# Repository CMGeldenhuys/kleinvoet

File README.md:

# Kleinvoet

*Kleinvoet* is a self-contained low-cost passive acoustic monitoring device.
The recorder was initially designed for distributed infrasonic (8Hz)
localisation, and features accurate temporal synchronisation through the use of
an onboard GNSS module.

The recorder is capable of 24-bit stereo recording at a variable sampling rate
of 8kHz to 192kHz.  The recordings along with timestamp and operational log
information is stored on a microSD card.  The recordings are stored as a series of
256MiB WAV files.

Firmware is available at [CMGeldenhuys/kleinvoet-firmware](https://github.com/CMGeldenhuys/kleinvoet-firmware).
All relevant production files such as panelised gerbers, bill of materials and work orders can be found in the `production` folder in the repo.
Additionally, the PCB layout and schematics for the Kleinvoet recorders can be found in the `docs/pcb_single`, `docs/pcb_panel` and `docs/schematics` directories, respectively.

## Example Recordings

- [Artificial elephant call](docs/rec/elephant_call_1000hz_lpf_normalised.wav) (recorded 150m from source, 1000Hz low pass filtered and normalised)

## SD Card Recommendations

In order to keep cost down, Kleinvoet does not make use of external SRAM. As such
the I/O buffer is limited to the internal SRAM of the MCU. It is thus
recommended using a class-10 high quality microSD card. Before a long-running
experiment it is also recommended to do a "low-level" format of the microSD
card. This will improve the write performance which is required at higher
sampling rates.

## Assembly

To assemble a Kleinvoet node, one will require all the electronic
components listed in the bill of materials (BOM), as well as have the necessary
PCBs manufactured. The provided gerber files can be sent directly to most PCB
fabrication houses. To assemble the boards, one can use either hot-air or plate
reflow soldering methods. The [interactive BOM](bom/ibom.html) might be useful
when placing the components manually.

| PCB | Back | Front |
| --- | --- | --- |
|Main Board|  |  |
|GNSS Board|  |  |
|Microphone Board|  |  |

Once all the components have been soldered to their respective boards, the
firmware can be flashed to the MCU using an [ST
Link](https://www.st.com/en/development-tools/st-link-v2.html)
debugger/programmer. However, not tested, any JTAG debugger/programmer should
work. There are also open-source projects that use another STM32 MCU as a
debugger/programmer ([blackmagic
probe](https://github.com/blackmagic-debug/blackmagic)).

Once programmed, proceed by connecting the GNSS header (marked on the respective
PCBs) of the main board to the GNSS daughter board. Note, this connector can be
reversed and the user should double-check that the **SYNC** pin (marked with an
triangle) on the main board is connected to the **SYNC** pin of the GNSS board.
If your use case does not require timestamping, the GNSS board can be omitted.
Next, connect the microphone boards to their respective channels, marked on the
main board's PCB as **CH1** and **CH2**. These connectors are keyed, and thus
It can only be connected one way.

If the user chooses to omit the weatherproof housing, Kleinvoet can be held
together with two rubber bands. The notches on the main and GNSS boards snap
together with the holes in the microphone boards to form a cube.

In order to assemble the weatherproof housing, start by placing the LiPo battery
in the lid of the enclosure. Thread the battery lead through the hole of the
main PCB adaptor plate. Next, mount the plate to the lid, keeping the battery in
place. One can then proceed to mount the main PCB to the adaptor. Next mount
the GNSS adaptor plate in the bottom of the Bocube housing, and mount the GNSS
PCB to the adaptor. If using the windshielding, remove the backing paper and
paste it firmly over the microphone inlets, (Note, the MEMS microphones used are
bottom port microphone and thus the inlet port is on the bottom side of the PCB.
The area to place the shielding foam is marked by a hashed circle) Install the
microphone board spacers, ensuring that the mounting holes align properly. The
microphone board assembly can now be mounted to the inside of the Bocube
housing. Next, connect the individual daughter boards (GNSS and microphone PCBs)
to their respective connectors on the main board.

Insert a FAT32 formatted microSD card into the main board and plug in the
battery. The node will perform a self test, followed by a self configuration
stage and then begin recordings. This process might take up to 10 seconds. Once
the node is configured, a solid amber light will be illuminated. Please refer to
the troubleshooting section if this is not the case.

## Operation

### Startup Procedure

1. Ensure the device is powered off.
1. Insert a FAT32 formatted microSD into the main board.
1. Connect the battery to the main board.
1. Wait for the solid amber indicator LED.
1. (Optional) Close weatherproof housing.

### Shutdown Procedure

1. Press the **USER** button (marked on the PCB of the main board).
1. The status indicators should start flashing repeatedly.
1. Disconnect the battery.
1. Remove microSD card.

### Status Indicators
Each PCB contains a *RED* status LED, used to indicate that the board has power.
On the main PCB there are two running status indication LEDs (*AMBER* and *BLUE*).

When **running**, the *AMBER* LED will remain solid. Once a GNSS lock (both time
and location) is obtained, the *BLUE* LED will pulse briefly every 10 seconds
(default).

If an unrecoverable error has occurred, the two status LEDs (*AMBER* and *BLUE*),
will pulse is quick succession. In this case, the watchdog timer will trigger and
attempt to write the operational log and reset the device. During a catastrophic
failure it might not be possible to write to the microSD card depending on the
error that has occurred.

| State | Blue LED | Amber LED |
| --- | --- | --- |
| Start-up | Blink (1s) | Off |
| Recording | Solid | X |
| GNSS Lock | X | Blink (10s) |
| Catastrophic Error | Strobe | Strobe |

In the table above, '*X*' denotes a "do not care" or irrelevant status. In other
words, it is not an indication of the current device state.

### File Layout

After recording, the following file structure will be present on the microSD card of the respective node.

```
(root)
├── REC_1
│   ├── KV.LOG
│   ├── REC.WAV
│   ├── REC.W01
│   ├── REC.W02
│   ├── REC.W03
│   └── TS.CSV
├── REC_X
│   ├── KV.LOG
│   ├── REC.WXX
│   └── TS.CSV
└── CONF.INI (experimental)
```

Each recording will be stored as a WAVE file in the corresponding `REC_X`
folder. Where the recorder increments `X` for every subsequent recording made on
the device (e.g. `REC_1`, `REC_2` etc.). Inside each recording folder are the
files associated with that recording. Due to the limitation of the FAT32
filesystem each individual recording has to be split up across multiple WAVE
files (e.g.`REC.WAV`, `REC.W01`, etc.). By default, this is in 256 MiB chunks, but
is user configurable Contained in the header of each WAVE file is timestamping
and location information required to synchronise the nodes during offline
processing of the files. A granular log of the timestamping metadata is stored
in `TS.CSV`. A complete operational log is stored in `KV.LOG`, which might deem
useful in troubleshooting a faulty recording node. (Experimental) Currently the
node's configuration is compiled into the device firmware, however, there is a
experimental firmware branch that allows for the configuration to be stored on
the microSD. 

| File/Folder | Purpose |
| --- | --- |
| REC_X | Folder containing all files associated with the particular recording|
| KV.LOG | Operational log of recordings |
| TS.CSV | Timestamping metadata |
| REC.WXX | Audio recording stored as a WAVE file |
| CONF.INI | (Experimental) Runtime configuration file |

## Power Spectral Density Estimates

Provided below are a power spectral density estimates (PSD) generated using
Welch's method. The [Sennheiser MKH 8020](https://sennheiser.com/mkh-8020) was used as a reference microphone and
tested in an acoustically dampened recording studio. These results provide an
estimate of the recording device's frequency response and should not be used
as ground truth measurements where spectral magnitude accuracy is required.
For those types of experiments, we recommenced the use of calibrated reference
sound amplitude measurement equipment.

## Troubleshooting

First ensure the following:
- Power from USB-C not battery, all boards have a solid *RED* LED illuminated
- MicroSD Card is formatted as **FAT32** and inserted
- The respective daughter boards are correctly connected

Enable `LOG_DEST_TTY` in `config.h`. The operational log will be printed in
real-time to the serial console available on the debug/programming port. When
using an *ST Link* debugger, this serial port can be opened using
[Putty](https://www.putty.org/) on Windows, or with the following command on
Linux:
``` sh
screen -b 115200 /dev/ttyACM0
```
The serial port is configured to **115200** baud rate and the standard **8N1**
configuration. Please see the [firmware guide](firmware/README.md) for more
information on setting up the programming environment on a Linux-based system.

## Future Hardware Revisions

- [ ] Dedicated GNSS connector, instead of headers
- [ ] E-Ink Display
- [ ] DFU mode (program without probe)
- [ ] Improved low-power mode (deep sleep)
- [ ] Add BME280 Sensor (temperature, humidity, atmospheric pressure)
- [ ] Battery charging status detection
- [ ] Dedicated power switch
- [ ] External RAM (larger buffer, allows use with low-end SD cards)
- [ ] Allow non-LiPo batteries (eg. alkaline)

## Contributing

We welcome contributions to the project. Unfortunately, hardware cannot be
provided to contributors. However, the [STM32
Nucleo-F446RE](https://www.st.com/en/evaluation-tools/nucleo-f446re.html) can be
used as an firmware development alternative, and is readily available.

## Authors and Acknowledgements

- [Christiaan M. Geldenhuys](https://github.com/CMGeldenhuys)
- [Thomas R. Niesler](https://dsp.sun.ac.za/~trn)

This project formed part of research done by the [Electrical and Electronic
Engineering Department](https://www.ee.sun.ac.za/) at Stellenbosch University.

## License

The Kleinvoet project is licensed under the CERN Open Hardware License version 2
(strongly-reciprocal variant). The license agreement and copyright only partain
to the Kleinvoet recorder design. Third party CAD models and EDA footprints
remain under the original license agreement and copyright of the respective
intellectual property owners.

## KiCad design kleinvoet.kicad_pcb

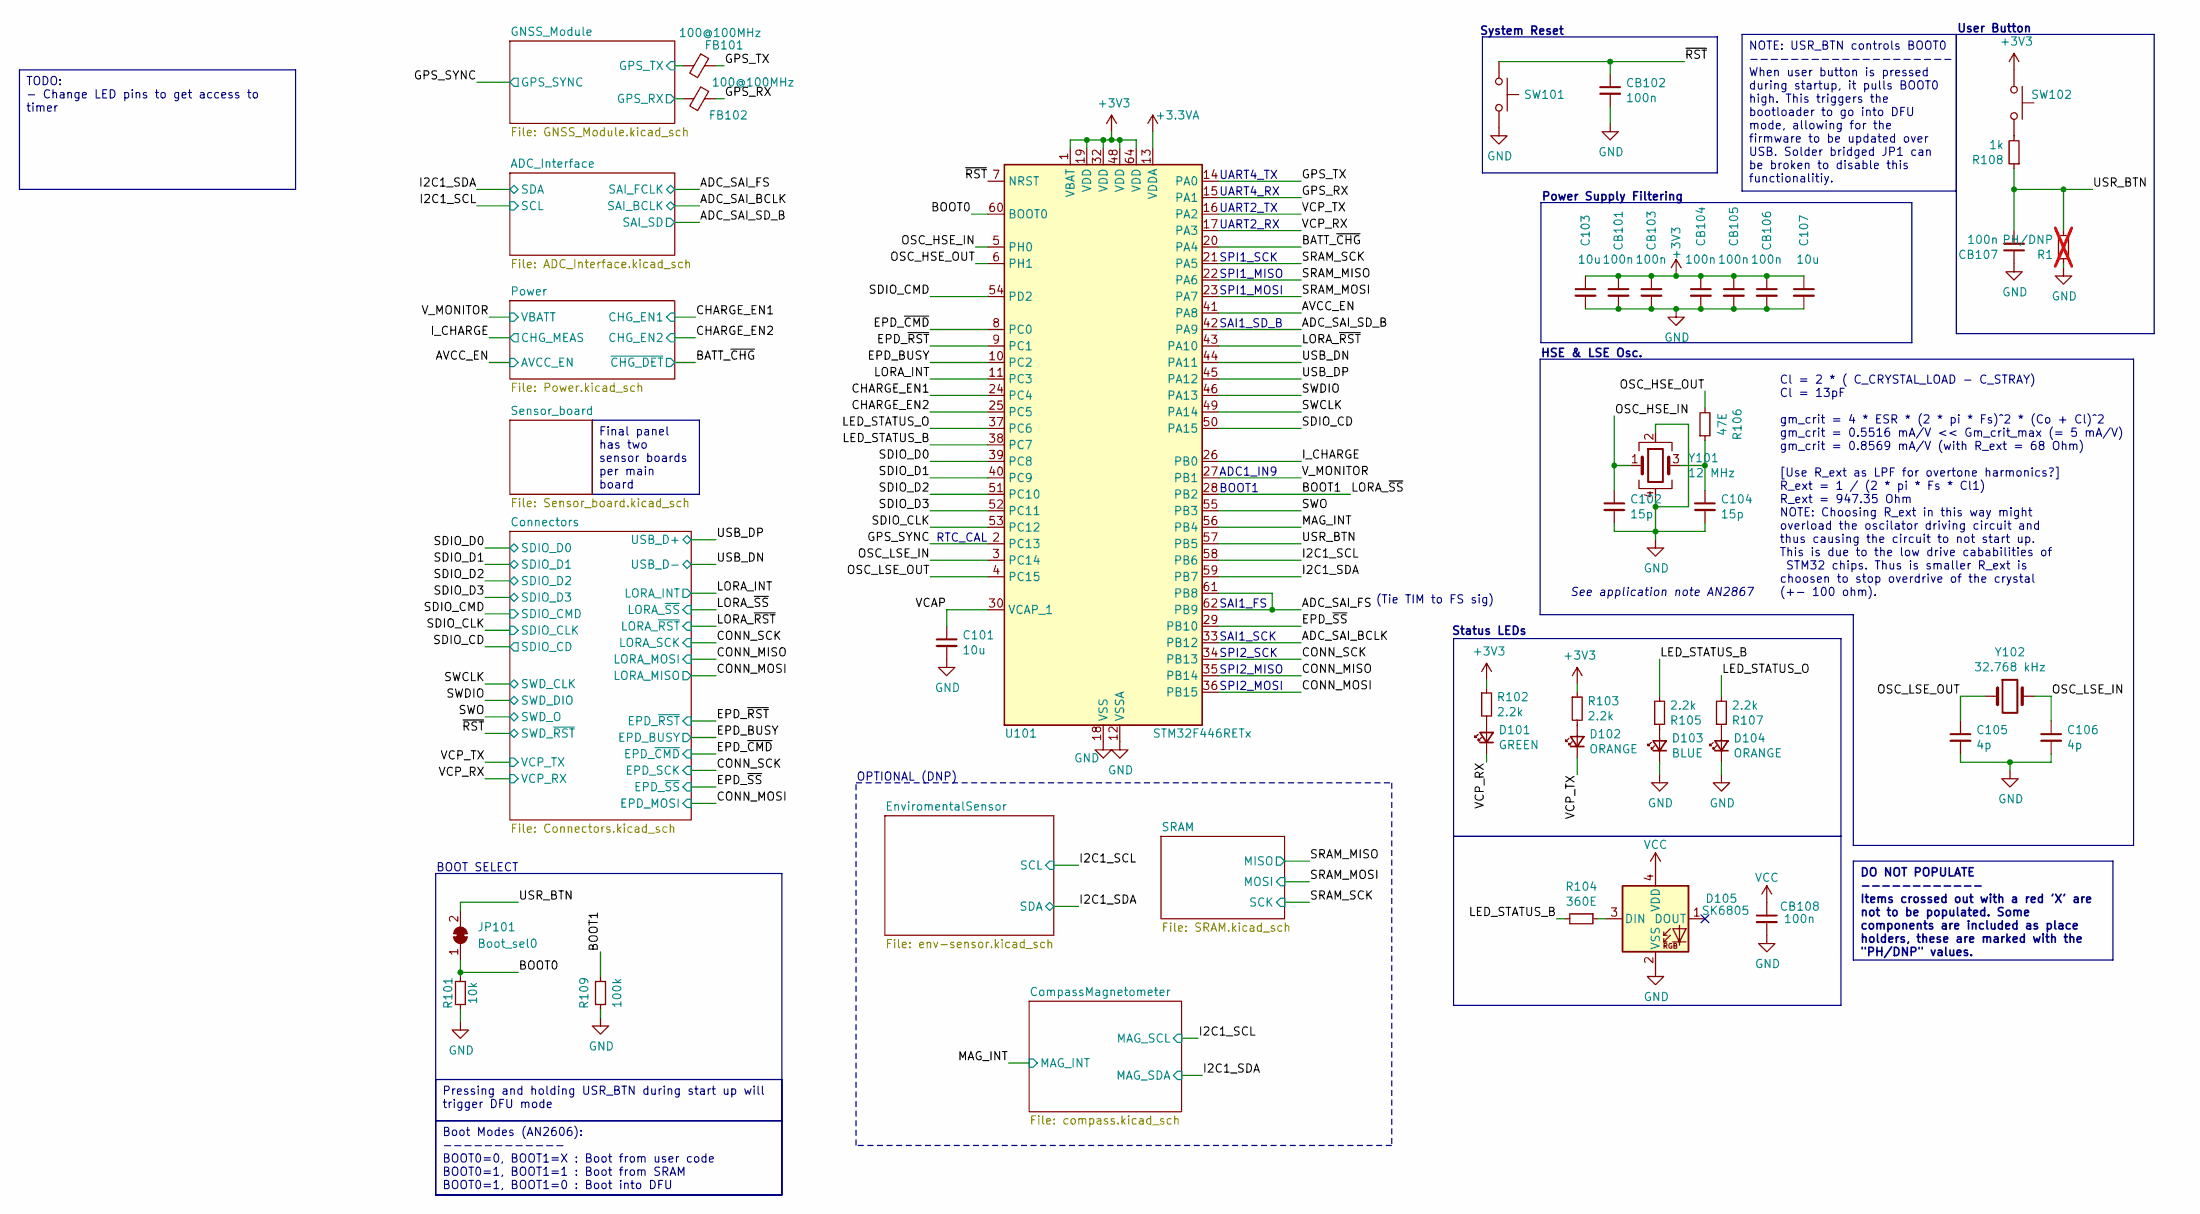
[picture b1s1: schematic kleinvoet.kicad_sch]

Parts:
C101, C103, C107: 10u; C_0402_1005Metric; MPN GRM155R60J106ME05D
C102, C104: 15p; C_0402_1005Metric; MPN GRM1555C1H150GA01D
C105, C106: 4p; C_0402_1005Metric; MPN GJM1555C1H4R0BB01D
CB101, CB102, CB103, CB104, CB105, CB106, CB107, CB108: 100n; C_0402_1005Metric; MPN C0402C104K8PACTU
D101: GREEN; LED_0603_1608Metric_Pad1.05x0.95mm_HandSolder; MPN SMLD12EN1WT86
D102: ORANGE; LED_0603_1608Metric_Pad1.05x0.95mm_HandSolder; MPN SML-D12D8WT86C
D103: BLUE; LED_0603_1608Metric; MPN SMLD12BN1WT86
D104: ORANGE; LED_0603_1608Metric; MPN SML-D12D8WT86C
D105: SK6805; LED_SK6805_PLCC4_2.4x2.7mm_P1.3mm; MPN SK6805-2427 (ALT: 485-4492, 1528-2291-N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
FB101, FB102: 100@100MHz; L_0402_1005Metric; MPN BLM15HD102SN1D
JP101: Boot_sel0; SolderJumper-2_P1.3mm_Bridged_RoundedPad1.0x1.5mm
R1: PH/DNP; R_0402_1005Metric; not fitted
R101: 10k; R_0402_1005Metric; MPN RT0402FRE1310KL
R102, R103, R105, R107: 2.2k; R_0402_1005Metric; MPN RT0402FRE072K2L
R104: 360E; R_0402_1005Metric; MPN RT0402FRE07360RL
R106: 47E; R_0402_1005Metric; MPN RT0402FRE0747RL
R108: 1k; R_0402_1005Metric; MPN RT0402FRE071KL
R109: 100k; R_0402_1005Metric; MPN RT0402FRE07100KL
SW101: RESET; SW_Tactile_SPST_NO_Straight_CK_PTS636Sx25SMTRLFS; MPN PTS636 SM25 SMTR LFS
SW102: USER; SW_Tactile_SPST_NO_Straight_CK_PTS636Sx25SMTRLFS; MPN PTS636 SM25 SMTR LFS
U101: STM32F446RETx; LQFP-64_10x10mm_P0.5mm; MPN STM32F446RCT6
Y101: 12 MHz; ECS-33B; MPN ECS-120-12-33-AEN-TR
Y102: 32.768 kHz; ECX-31B; MPN ECS-.327-7-34B-TR

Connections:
+3.3VA: U101.13 (VDDA); also elsewhere on the board
/ADC_SAI_BCLK: U101.33 (PB12); also elsewhere on the board
/ADC_SAI_FS: U101.61 (PB8), U101.62 (PB9); also elsewhere on the board
/ADC_SAI_SD_B: U101.42 (PA9); also elsewhere on the board
/AVCC_EN: U101.41 (PA8); also elsewhere on the board
/BATT_~CHG: U101.20 (PA4); also elsewhere on the board
/BOOT0: JP101.1 (A), R101.1, U101.60 (BOOT0)
/BOOT1: R109.2, U101.28 (PB2); also elsewhere on the board
/CHARGE_EN1: U101.24 (PC4); also elsewhere on the board
/CHARGE_EN2: U101.25 (PC5); also elsewhere on the board
/CONN_MISO: U101.35 (PB14); also elsewhere on the board
/CONN_MOSI: U101.36 (PB15); also elsewhere on the board
/CONN_SCK: U101.34 (PB13); also elsewhere on the board
/EPD_BUSY: U101.10 (PC2); also elsewhere on the board
/EPD_~CMD: U101.8 (PC0); also elsewhere on the board
/EPD_~RST: U101.9 (PC1); also elsewhere on the board
/EPD_~SS: U101.29 (PB10); also elsewhere on the board
/GNSS_Module/GPS_RX: FB102.1; also elsewhere on the board
/GNSS_Module/GPS_TX: FB101.1; also elsewhere on the board
/GPS_RX: FB102.2, U101.15 (PA1)
/GPS_SYNC: U101.2 (PC13); also elsewhere on the board
/GPS_TX: FB101.2, U101.14 (PA0)
/I_CHARGE: U101.26 (PB0); also elsewhere on the board
/LED_STATUS_B: R104.2, R105.2, U101.38 (PC7)
/LED_STATUS_O: R107.2, U101.37 (PC6)
/LORA_INT: U101.11 (PC3); also elsewhere on the board
/LORA_~RST: U101.43 (PA10); also elsewhere on the board
/MAG_INT: U101.56 (PB4); also elsewhere on the board
/OSC_HSE_IN: C102.1, U101.5 (PH0), Y101.1
/OSC_HSE_OUT: R106.2, U101.6 (PH1)
/OSC_LSE_IN: C106.1, U101.3 (PC14), Y102.2
/OSC_LSE_OUT: C105.1, U101.4 (PC15), Y102.1
/SDIO_CD: U101.50 (PA15); also elsewhere on the board
/SDIO_CLK: U101.53 (PC12); also elsewhere on the board
/SDIO_CMD: U101.54 (PD2); also elsewhere on the board
/SDIO_D0: U101.39 (PC8); also elsewhere on the board
/SDIO_D1: U101.40 (PC9); also elsewhere on the board
/SDIO_D2: U101.51 (PC10); also elsewhere on the board
/SDIO_D3: U101.52 (PC11); also elsewhere on the board
/SRAM_MISO: U101.22 (PA6); also elsewhere on the board
/SRAM_MOSI: U101.23 (PA7); also elsewhere on the board
/SRAM_SCK: U101.21 (PA5); also elsewhere on the board
/SWCLK: U101.49 (PA14); also elsewhere on the board
/SWDIO: U101.46 (PA13); also elsewhere on the board
/SWO: U101.55 (PB3); also elsewhere on the board
/USB_DN: U101.44 (PA11); also elsewhere on the board
/USB_DP: U101.45 (PA12); also elsewhere on the board
/USR_BTN: CB107.2, JP101.2 (B), R1.2, R108.1, U101.57 (PB5)
/VCAP: C101.1, U101.30 (VCAP_1)
/VCP_RX: D101.1 (K), U101.17 (PA3); also elsewhere on the board
/VCP_TX: D102.1 (K), U101.16 (PA2); also elsewhere on the board
/V_MONITOR: U101.27 (PB1); also elsewhere on the board
/~RST: CB102.1, SW101.1, U101.7 (NRST); also elsewhere on the board
GND: C101.2, C102.2, C103.2, C104.2, C105.2, C106.2, C107.2, CB101.2, CB102.2, CB103.2, CB104.2, CB105.2, CB106.2, CB107.1, CB108.2, D103.1 (K), D104.1 (K), D105.2 (VSS), R1.1, R101.2, R109.1, SW101.2, U101.12 (VSSA), U101.18 (VSS), U101.31 (VSS), U101.47 (VSS), U101.63 (VSS), Y101.2, Y101.4; also elsewhere on the board
unnamed: C104.1, R106.1, Y101.3
unnamed: D101.2 (A), R102.2
unnamed: D102.2 (A), R103.2
unnamed: D103.2 (A), R105.1
unnamed: D104.2 (A), R107.1
unnamed: D105.3 (DIN), R104.1
unnamed: R108.2, SW102.2
VCC: CB108.1, D105.4 (VDD); also elsewhere on the board

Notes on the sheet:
BOOT SELECT
(Tie TIM to FS sig)
Cl = 2 * ( C_CRYSTAL_LOAD - C_STRAY) Cl = 13pF gm_crit = 4 * ESR * (2 * pi * Fs)^2 * (Co + Cl)^2 gm_crit = 0.5516 mA/V << Gm_crit_max (= 5 mA/V) gm_crit = 0.8569 mA/V (with R_ext = 68 Ohm) [Use R_ext as LPF for overtone harmonics?] R_ext = 1 / (2 * pi * Fs * Cl1) R_ext = 947.35 Ohm NOTE: Choosing R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
SPI1_MISO
User Button
UART2_TX
UART4_TX
BOOT1
System Reset
SAI1_SCK
UART4_RX
SAI1_SD_B
Status LEDs
OPTIONAL (DNP)
ADC1_IN9
SPI1_SCK
SAI1_FS
HSE & LSE Osc.
UART2_RX
SPI2_MOSI
Power Supply Filtering
SPI2_MISO
RTC_CAL
SPI2_SCK
SPI1_MOSI
See application note AN2867
Pressing and holding USR_BTN during start up will trigger DFU mode
DO NOT POPULATE ------------ Items crossed out with a red 'X' are not to be populated. Some components are included as place holders, these are marked with the "PH/DNP" values.
TODO: - Change LED pins to get access to timer
NOTE: USR_BTN controls BOOT0 -------------------- When user button is pressed during startup, it pulls BOOT0 high. This triggers the bootloader to go into DFU mode, allowing for the firmware to be updated over USB. Solder bridged JP1 can be broken to disable this functionalitiy.
Boot Modes (AN2606): ------------ BOOT0=0, BOOT1=X : Boot from user code BOOT0=1, BOOT1=1 : Boot from SRAM BOOT0=1, BOOT1=0 : Boot into DFU
Final panel has two sensor boards per main board

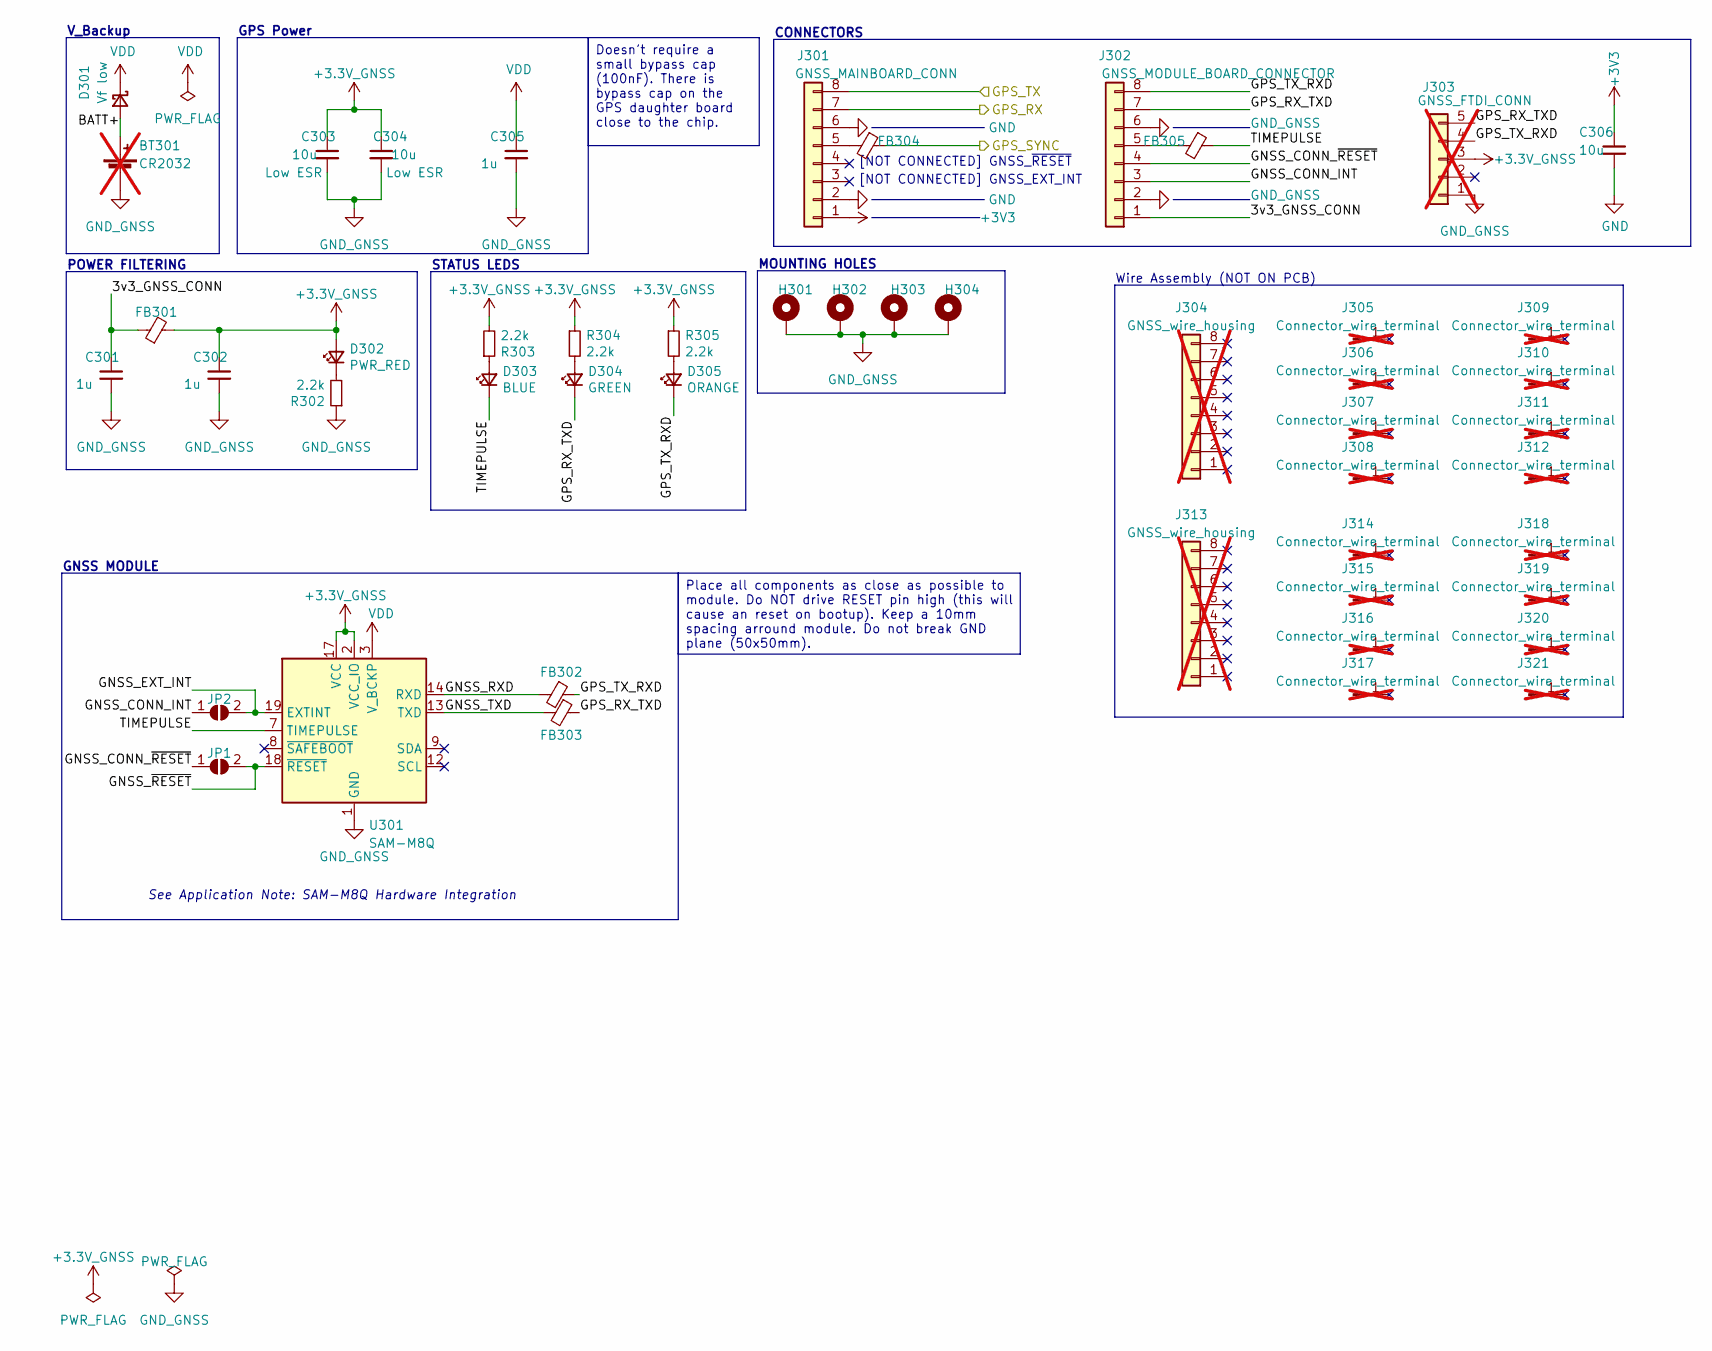
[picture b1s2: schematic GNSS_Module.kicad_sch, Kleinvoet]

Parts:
BT301: CR2032; BatteryHolder_Keystone_3002_1x2032; MPN 2898; not fitted
C301, C302, C305: 1u; C_0402_1005Metric; MPN C0402C105K9PACTU
C303, C304, C306: 10u; C_0402_1005Metric; MPN GRM155R60J106ME05D
D301: Vf low; D_SOD-523; MPN RB520S30T1G
D302: PWR_RED; LED_0603_1608Metric; MPN SML-D12U8WT86C
D303: BLUE; LED_0603_1608Metric; MPN SMLD12BN1WT86
D304: GREEN; LED_0603_1608Metric; MPN SMLD12EN1WT86
D305: ORANGE; LED_0603_1608Metric; MPN SML-D12D8WT86C
FB301, FB302, FB303, FB304, FB305: 100@100MHz; L_0402_1005Metric; MPN BLM15HD102SN1D
H301, H302, H303, H304: MountingHole_Pad; MountingHole_3.2mm_M3_Pad_Via
J301: GNSS_MAINBOARD_CONN; Connector_Amphenol_10114828-xxx08LF_Vertical; MPN 10114828-11108LF
J302: GNSS_MODULE_BOARD_CONNECTOR; Connector_Amphenol_10114828-xxx08LF_Vertical; MPN 10114828-11108LF
J303: GNSS_FTDI_CONN; PinHeader_1x05_P2.54mm_Vertical; not fitted
J304, J313: GNSS_wire_housing; MPN 10114826-00008LF; not fitted
J305, J306, J307, J308, J309, J310, J311, J312, J314, J315, J316, J317, J318, J319, J320, J321: Connector_wire_terminal; MPN 10114827-002LF; not fitted
JP1: GNSS_CONN_~{RESET}_SEL; SolderJumper-2_P1.3mm_Open_RoundedPad1.0x1.5mm
JP2: GNSS_CONN_EXT_INT_SEL; SolderJumper-2_P1.3mm_Open_RoundedPad1.0x1.5mm
R302, R303, R304, R305: 2.2k; R_0402_1005Metric; MPN RT0402FRE072K2L
U301: SAM-M8Q; ublox_SAM-M8Q; MPN SAM-M8Q

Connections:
+3.3V_GNSS: C302.1, C303.1, C304.1, D302.2 (A), FB301.2, J303.3, R303.2, R304.1, R305.1, U301.2 (VCC_IO), U301.17 (VCC)
/GNSS_Module/3v3_GNSS_CONN: C301.1, FB301.1, J302.1
/GNSS_Module/BATT+: BT301.1 (+), D301.2 (A)
/GNSS_Module/GNSS_CONN_INT: J302.3, JP2.1 (A)
/GNSS_Module/GNSS_CONN_~RESET: J302.4, JP1.1 (A)
/GNSS_Module/GNSS_EXT_INT: JP2.2 (B), U301.19 (EXTINT)
/GNSS_Module/GNSS_RXD: FB302.2, U301.14 (RXD)
/GNSS_Module/GNSS_TXD: FB303.2, U301.13 (TXD)
/GNSS_Module/GNSS_~RESET: JP1.2 (B), U301.18 (~RESET)
/GNSS_Module/GPS_RX: J301.7; also elsewhere on the board
/GNSS_Module/GPS_RX_TXD: D304.1 (K), FB303.1, J302.7, J303.5
/GNSS_Module/GPS_TX: J301.8; also elsewhere on the board
/GNSS_Module/GPS_TX_RXD: D305.1 (K), FB302.1, J302.8, J303.4
/GNSS_Module/TIMEPULSE: D303.1 (K), FB305.1, U301.7 (TIMEPULSE)
/GPS_SYNC: FB304.1; also elsewhere on the board
GND: C306.2, J301.2, J301.6; also elsewhere on the board
GND_GNSS: BT301.2 (-), C301.2, C302.2, C303.2, C304.2, C305.2, H301.1, H302.1, H303.1, H304.1, J302.2, J302.6, J303.1, R302.1, U301.1 (GND), U301.4 (GND), U301.5 (GND), U301.6 (GND), U301.10 (GND), U301.11 (GND), U301.15 (GND), U301.16 (GND), U301.20 (GND)
unnamed: D302.1 (K), R302.2
unnamed: D303.2 (A), R303.1
unnamed: D304.2 (A), R304.2
unnamed: D305.2 (A), R305.2
unnamed: FB304.2, J301.5
unnamed: FB305.2, J302.5
VDD: C305.1, D301.1 (K), U301.3 (V_BCKP)

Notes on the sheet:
V_Backup
POWER FILTERING
See Application Note: SAM-M8Q Hardware Integration
CONNECTORS
[NOT CONNECTED] GNSS_EXT_INT
GPS Power
[NOT CONNECTED] GNSS_~{RESET}
MOUNTING HOLES
GNSS MODULE
STATUS LEDS
Wire Assembly (NOT ON PCB)
Place all components as close as possible to module. Do NOT drive RESET pin high (this will cause an reset on bootup). Keep a 10mm spacing arround module. Do not break GND plane (50x50mm).
Doesn't require a small bypass cap (100nF). There is bypass cap on the GPS daughter board close to the chip.

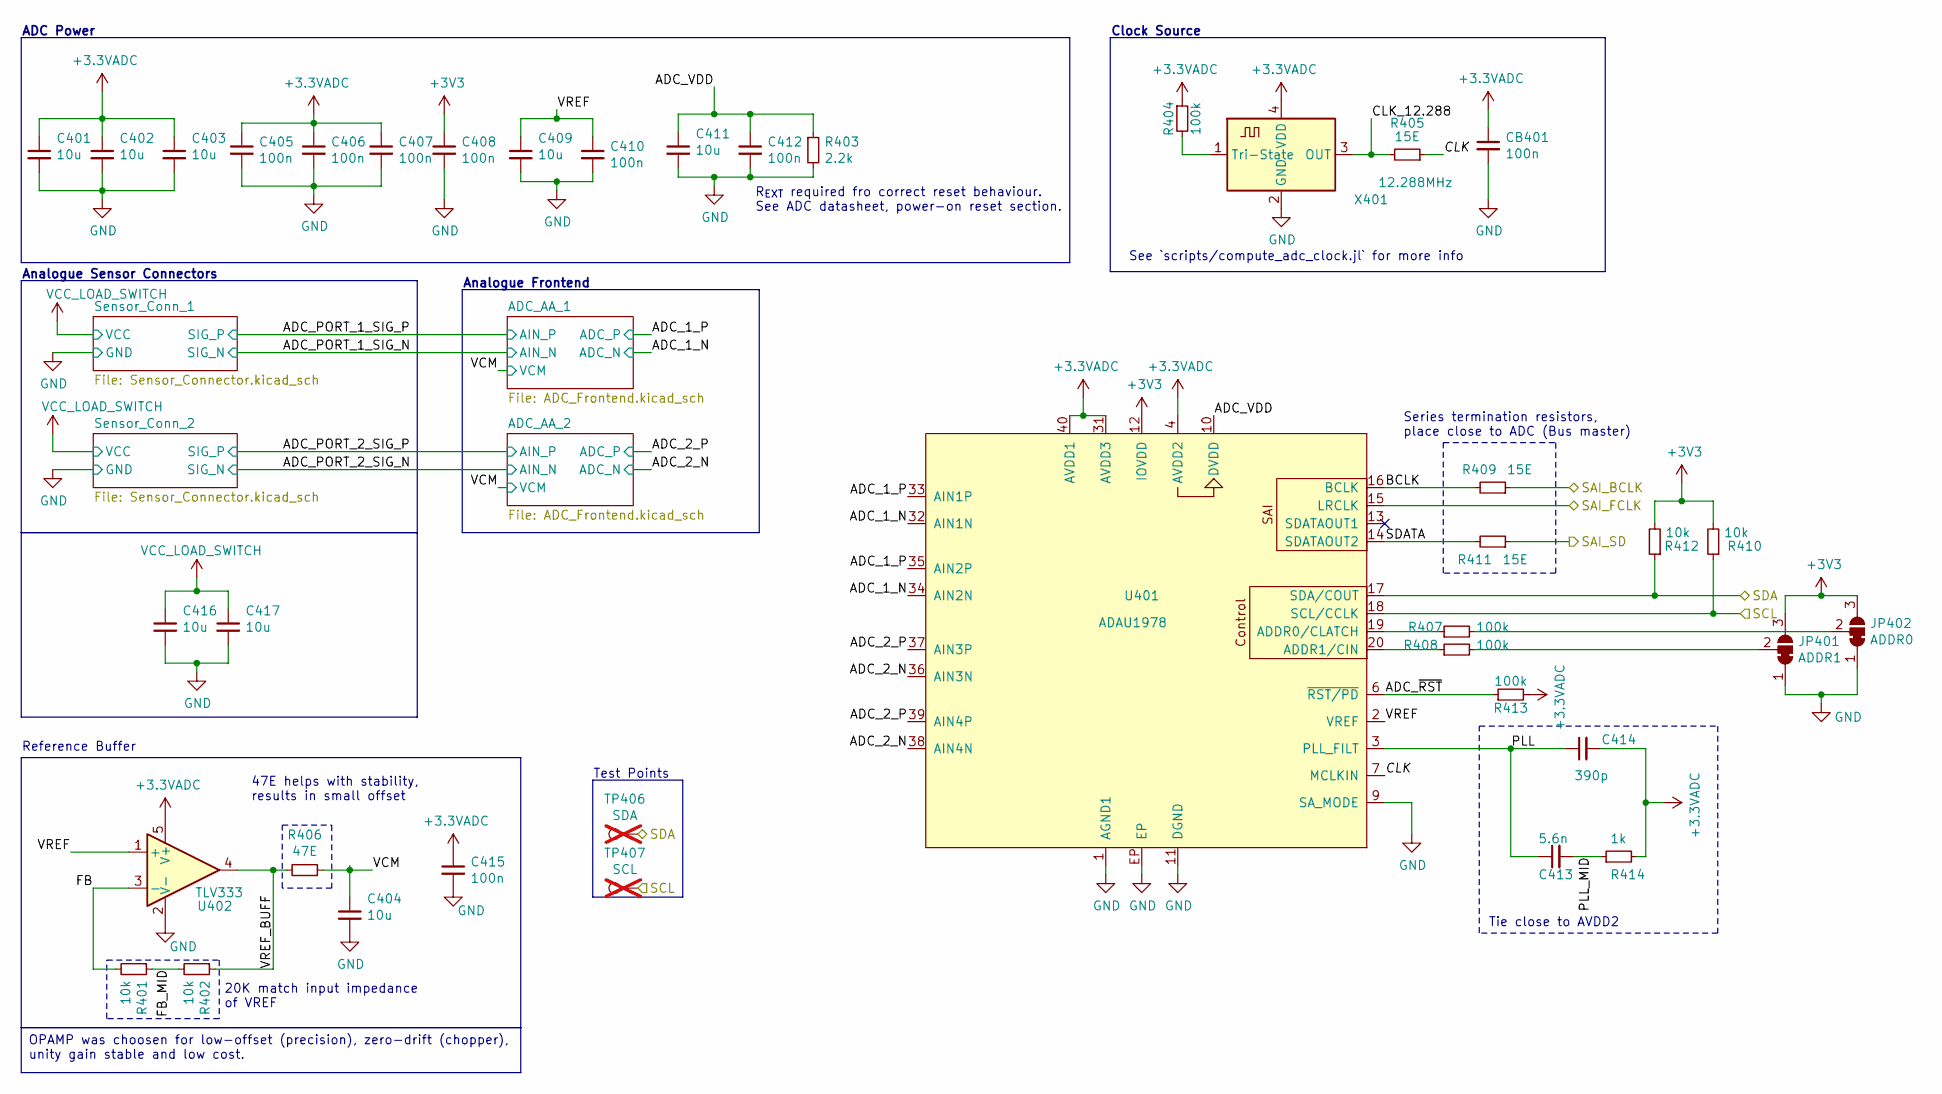
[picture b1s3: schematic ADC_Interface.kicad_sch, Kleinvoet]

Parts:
C401, C402, C403, C404, C409, C411, C416, C417: 10u; C_0402_1005Metric; MPN GRM155R60J106ME05D
C405, C406, C407, C408, C410, C412, C415: 100n; C_0402_1005Metric; MPN C0402C104K8PACTU
C413: 5.6n; C_0402_1005Metric; MPN GRM1555C1H562JE01D
C414: 390p; C_0402_1005Metric; MPN GRM1555C1H391JA01D
CB401: 100n; C_0402_1005Metric; MPN C0402C104K8PACTU
JP401: ADDR1; SolderJumper-3_P1.3mm_Bridged12_RoundedPad1.0x1.5mm_NumberL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
JP402: ADDR0; SolderJumper-3_P1.3mm_Bridged12_RoundedPad1.0x1.5mm_NumberL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
R401, R402, R410, R412: 10k; R_0402_1005Metric; MPN RT0402FRE1310KL
R403: 2.2k; R_0402_1005Metric; MPN RT0402FRE072K2L
R404, R407, R408, R413: 100k; R_0402_1005Metric; MPN RT0402FRE07100KL
R405, R409, R411: 15E; R_0402_1005Metric; MPN RT0402FRE0715RL
R406: 47E; R_0402_1005Metric; MPN RT0402FRE0747RL
R414: 1k; R_0402_1005Metric; MPN RT0402FRE071KL
TP406: SDA; TestPoint_Pad_D1.0mm; not fitted
TP407: SCL; TestPoint_Pad_D1.0mm; not fitted
U401: ADAU1978; LFCSP-WQ-40-1EP_6x6mm_P0.5_CP-40-14; MPN ADAU1978WBCPZ-RL
U402: TLV333; Texas_R-PDSO-G5_DCK-5; MPN TLV333IDCKR
X401: 12.288MHz; ECS-TXO-3225MV; MPN ECS-TXO-3225MV-122.8-TR

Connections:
+3.3VADC: C401.1, C402.1, C403.1, C405.1, C406.1, C407.1, C414.2, C415.1, CB401.1, R404.1, R413.2, R414.2, U401.4 (AVDD2), U401.31 (AVDD3), U401.40 (AVDD1), U402.5 (V+), X401.4 (VDD); also elsewhere on the board
/ADC_Interface/ADC_1_N: U401.32 (AIN1N), U401.34 (AIN2N); also elsewhere on the board
/ADC_Interface/ADC_1_P: U401.33 (AIN1P), U401.35 (AIN2P); also elsewhere on the board
/ADC_Interface/ADC_2_N: U401.36 (AIN3N), U401.38 (AIN4N); also elsewhere on the board
/ADC_Interface/ADC_2_P: U401.37 (AIN3P), U401.39 (AIN4P); also elsewhere on the board
/ADC_Interface/ADC_VDD: C411.1, C412.1, R403.1, U401.10 (DVDD)
/ADC_Interface/ADC_~RST: R413.1, U401.6 (~RST/PD)
/ADC_Interface/BCLK: R409.2, U401.16 (BCLK)
/ADC_Interface/CLK: R405.1, U401.7 (MCLKIN)
/ADC_Interface/CLK_12.288: R405.2, X401.3 (OUT)
/ADC_Interface/FB: R401.2, U402.3 (-)
/ADC_Interface/FB_MID: R401.1, R402.2
/ADC_Interface/PLL: C413.1, C414.1, U401.3 (PLL_FILT)
/ADC_Interface/PLL_MID: C413.2, R414.1
/ADC_Interface/SDATA: R411.2, U401.14 (SDATAOUT2)
/ADC_Interface/VCM: C404.1, R406.1; also elsewhere on the board
/ADC_Interface/VREF: C409.1, C410.1, U401.2 (VREF), U402.1 (+)
/ADC_Interface/VREF_BUFF: R402.1, R406.2, U402.4
/ADC_SAI_BCLK: R409.1; also elsewhere on the board
/ADC_SAI_FS: U401.15 (LRCLK); also elsewhere on the board
/ADC_SAI_SD_B: R411.1; also elsewhere on the board
GND: C401.2, C402.2, C403.2, C404.2, C405.2, C406.2, C407.2, C408.2, C409.2, C410.2, C411.2, C412.2, C415.2, C416.2, C417.2, CB401.2, JP401.1 (A), JP402.1 (A), R403.2, U401.1 (AGND1), U401.5 (AGND2), U401.9 (SA_MODE), U401.11 (DGND), U401.21 (AGND3), U401.22 (AGND4), U401.28 (AGND5), U401.29 (AGND6), U401.EP, U402.2 (V-), X401.2 (GND); also elsewhere on the board
unnamed: JP401.2 (C), R408.2
unnamed: JP402.2 (C), R407.2
unnamed: R407.1, U401.19 (ADDR0/CLATCH)
unnamed: R408.1, U401.20 (ADDR1/CIN)
unnamed: R404.2, X401.1 (Tri-State)
VCC_LOAD_SWITCH: C416.1, C417.1; also elsewhere on the board

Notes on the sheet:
47E helps with stability, results in small offset
See `scripts/compute_adc_clock.jl` for more info
ADC Power
20K match input impedance of VREF
Clock Source
Test Points
Analogue Frontend
R_{EXT} required fro correct reset behaviour. See ADC datasheet, power-on reset section.
Reference Buffer
Series termination resistors, place close to ADC (Bus master)
Tie close to AVDD2
Analogue Sensor Connectors
OPAMP was choosen for low-offset (precision), zero-drift (chopper), unity gain stable and low cost.

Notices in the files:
ADC_Frontend.kicad_sch:
License: CERN-OHL-S-2.0
